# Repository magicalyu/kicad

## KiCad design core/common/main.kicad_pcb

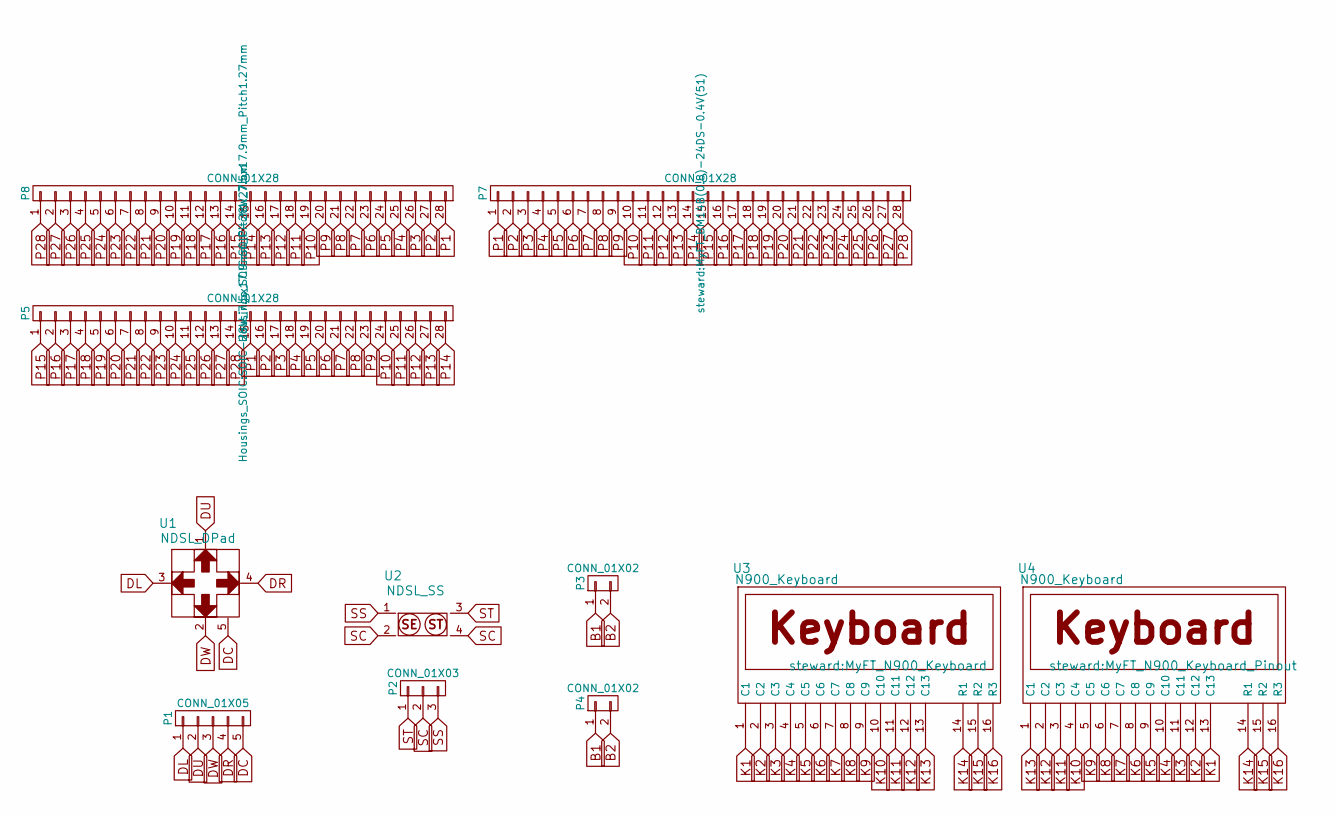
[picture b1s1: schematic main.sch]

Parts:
P1: CONN_01X05; MyFT_SIM5
P2: CONN_01X03; MyFT_SIM3
P3: CONN_01X02; SW_SPST_EVPBF
P4: CONN_01X02; MyFT_SIM2
P5, P8: CONN_01X28; SOIC-28W_7.5x17.9mm_Pitch1.27mm
P7: CONN_01X28; MyFT_BM14B(0.8)-24DS-0.4V(51)
U1: NDSL_DPad; MyFT_NDSL_DPad
U2: NDSL_SS; MyFT_NDSL_SS
U3: N900_Keyboard; MyFT_N900_Keyboard
U4: N900_Keyboard; MyFT_N900_Keyboard_Pinout

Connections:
B1: P3.1, P4.1
B2: P3.2, P4.2
DC: P1.5, U1.5
DL: P1.1, U1.3
DR: P1.4, U1.4
DU: P1.2, U1.1
DW: P1.3, U1.2
K1: U3.1 (C1), U4.13 (C13)
K2: U3.2 (C2), U4.12 (C12)
K3: U3.3 (C3), U4.11 (C11)
K4: U3.4 (C4), U4.10 (C10)
K5: U3.5 (C5), U4.9 (C9)
K6: U3.6 (C6), U4.8 (C8)
K7: U3.7 (C7), U4.7 (C7)
K8: U3.8 (C8), U4.6 (C6)
K9: U3.9 (C9), U4.5 (C5)
K10: U3.10 (C10), U4.4 (C4)
K11: U3.11 (C11), U4.3 (C3)
K12: U3.12 (C12), U4.2 (C2)
K13: U3.13 (C13), U4.1 (C1)
K14: U3.14 (R1), U4.14 (R1)
K15: U3.15 (R2), U4.15 (R2)
K16: U3.16 (R3), U4.16 (R3)
P1: P5.15, P7.1, P8.28
P2: P5.16, P7.2, P8.27
P3: P5.17, P7.3, P8.26
P4: P5.18, P7.4, P8.25
P5: P5.19, P7.5, P8.24
P6: P5.20, P7.6, P8.23
P7: P5.21, P7.7, P8.22
P8: P5.22, P7.8, P8.21
P9: P5.23, P7.9, P8.20
P10: P5.24, P7.10, P8.19
P11: P5.25, P7.11, P8.18
P12: P5.26, P7.12, P8.17
P13: P5.27, P7.13, P8.16
P14: P5.28, P7.14, P8.15
P15: P5.1, P7.15, P8.14
P16: P5.2, P7.16, P8.13
P17: P5.3, P7.17, P8.12
P18: P5.4, P7.18, P8.11
P19: P5.5, P7.19, P8.10
P20: P5.6, P7.20, P8.9
P21: P5.7, P7.21, P8.8
P22: P5.8, P7.22, P8.7
P23: P5.9, P7.23, P8.6
P24: P5.10, P7.24, P8.5
P25: P5.11, P7.25, P8.4
P26: P5.12, P7.26, P8.3
P27: P5.13, P7.27, P8.2
P28: P5.14, P7.28, P8.1
SC: P2.2, U2.2, U2.4
SS: P2.3, U2.1
ST: P2.1, U2.3

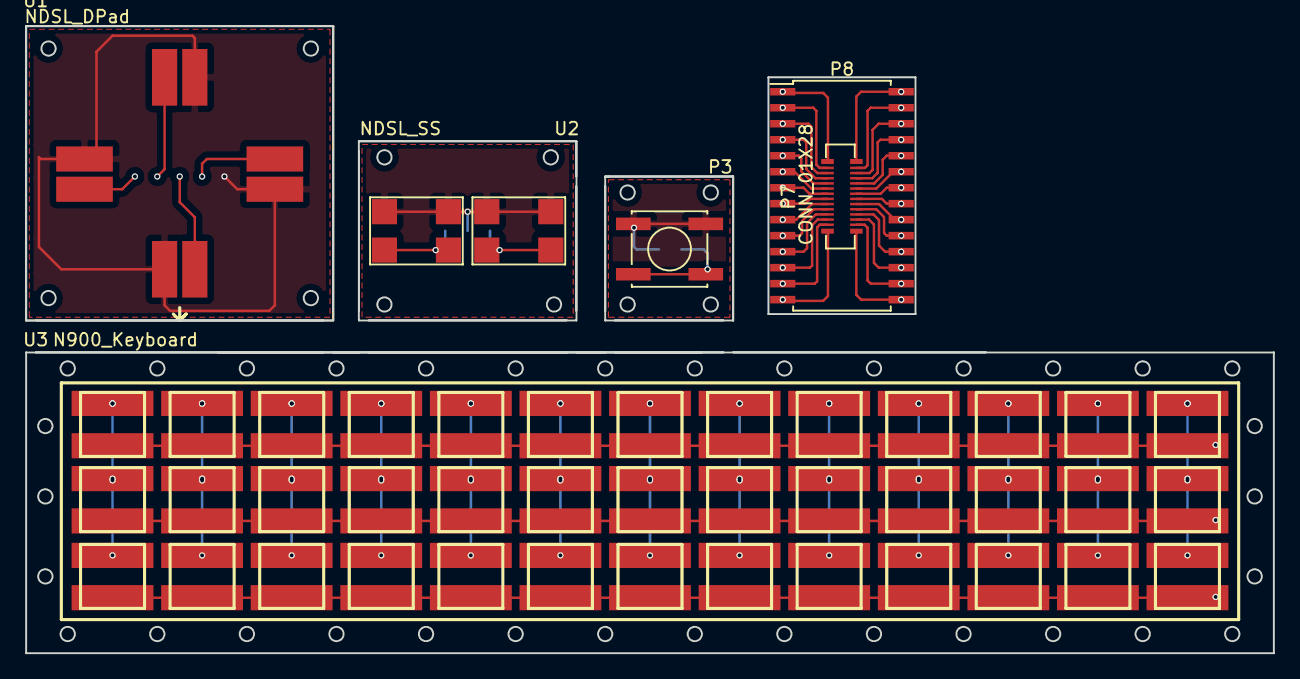
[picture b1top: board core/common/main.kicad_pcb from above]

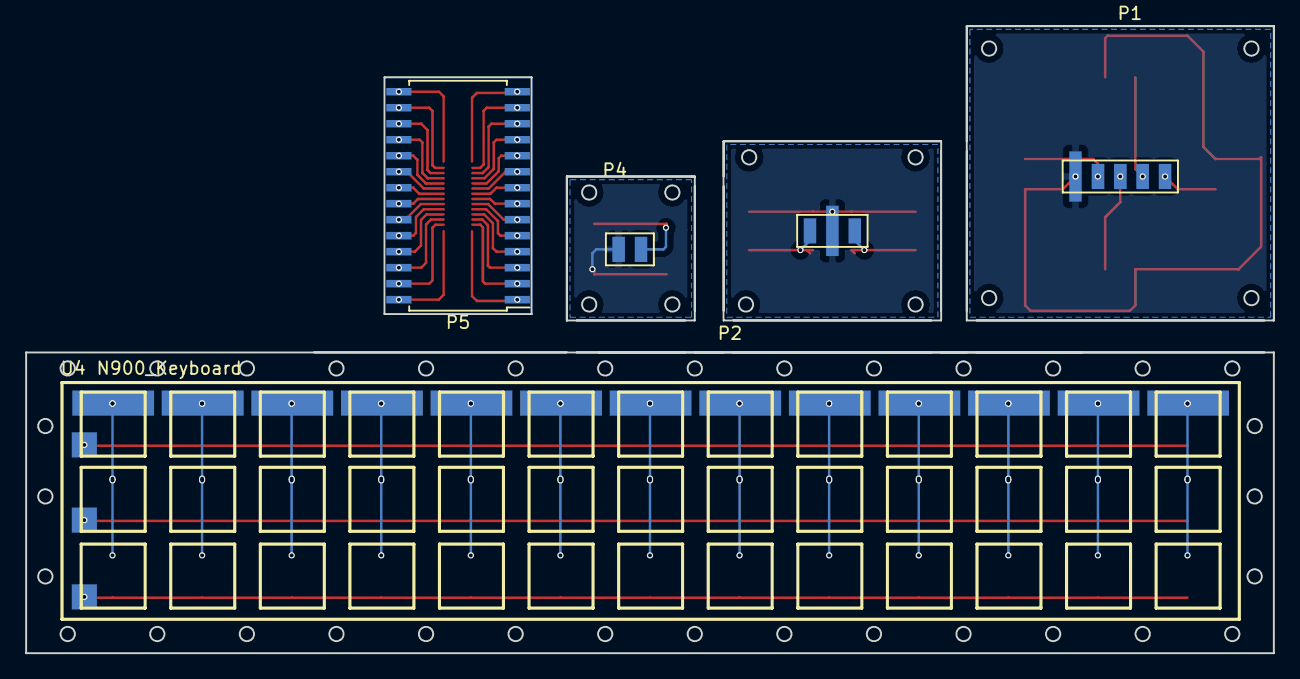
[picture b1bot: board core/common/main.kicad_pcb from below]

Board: 2 copper layers, 99.1 x 49.8 mm, 11 parts (5 on the bottom side), 54 nets.

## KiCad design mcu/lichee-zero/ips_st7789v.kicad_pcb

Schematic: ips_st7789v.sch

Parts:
P1: CONN_01X05
U1: IPS_2.4_240X320_ST7789V
U2: LICHEE_ZERO_LCD

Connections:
CS: P1.2, U1.8
DB0: U1.18, U2.23
DB1: U1.19, U2.24
DB2: U1.20, U2.25
DB3: U1.21, U2.26
DB4: U1.22, U2.27
DB5: U1.23, U2.28
DB6: U1.24, U2.15
DB7: U1.25, U2.16
DB8: U1.26, U2.17
DB9: U1.27, U2.18
DB10: U1.28, U2.19
DB11: U1.30, U2.20
DB12: U1.31, U2.7
DB13: U1.32, U2.8
DB14: U1.33, U2.9
DB15: U1.34, U2.10
DEN: U1.14, U2.34
GND: U1.1, U1.5, U1.17, U1.29, U1.37, U1.38, U1.39, U1.40, U1.41, U1.42, U1.43, U1.44, U1.45, U2.3
HSYNC: U1.13, U2.32
PCLK: U1.15, U2.30
RESET: P1.1, U1.7
SCL: P1.3, U1.9
SDI: P1.4, U1.16
SDO: P1.5, U1.35
VCC: U1.2, U1.3, U1.4, U1.6, U1.10, U1.11, U1.36, U2.4
VSYNC: U1.12, U2.33

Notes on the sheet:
PCB for LiChee_Zero LCD to 2.8" IPS ST7789V

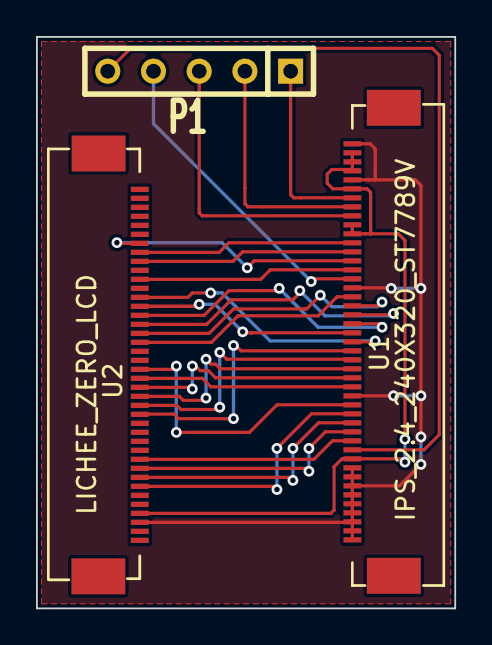
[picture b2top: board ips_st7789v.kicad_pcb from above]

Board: 2 copper layers, 23.2 x 31.8 mm, 3 parts (0 on the bottom side), 27 nets.

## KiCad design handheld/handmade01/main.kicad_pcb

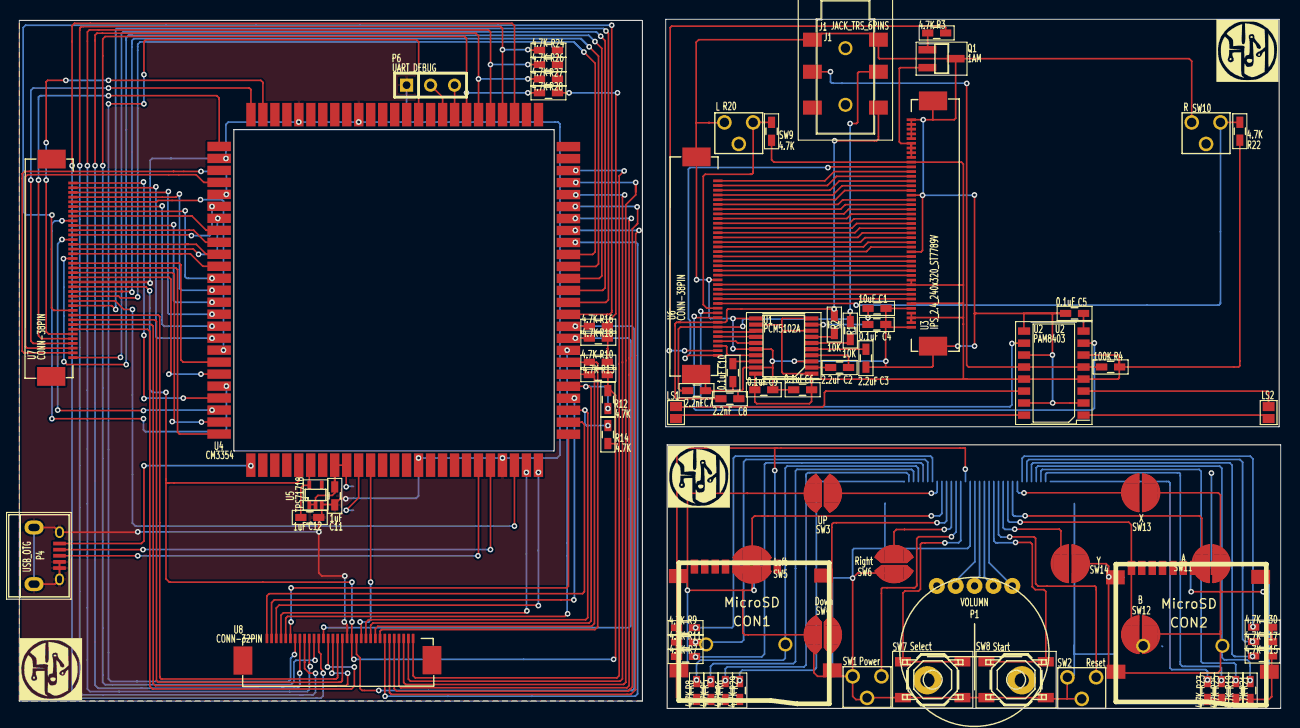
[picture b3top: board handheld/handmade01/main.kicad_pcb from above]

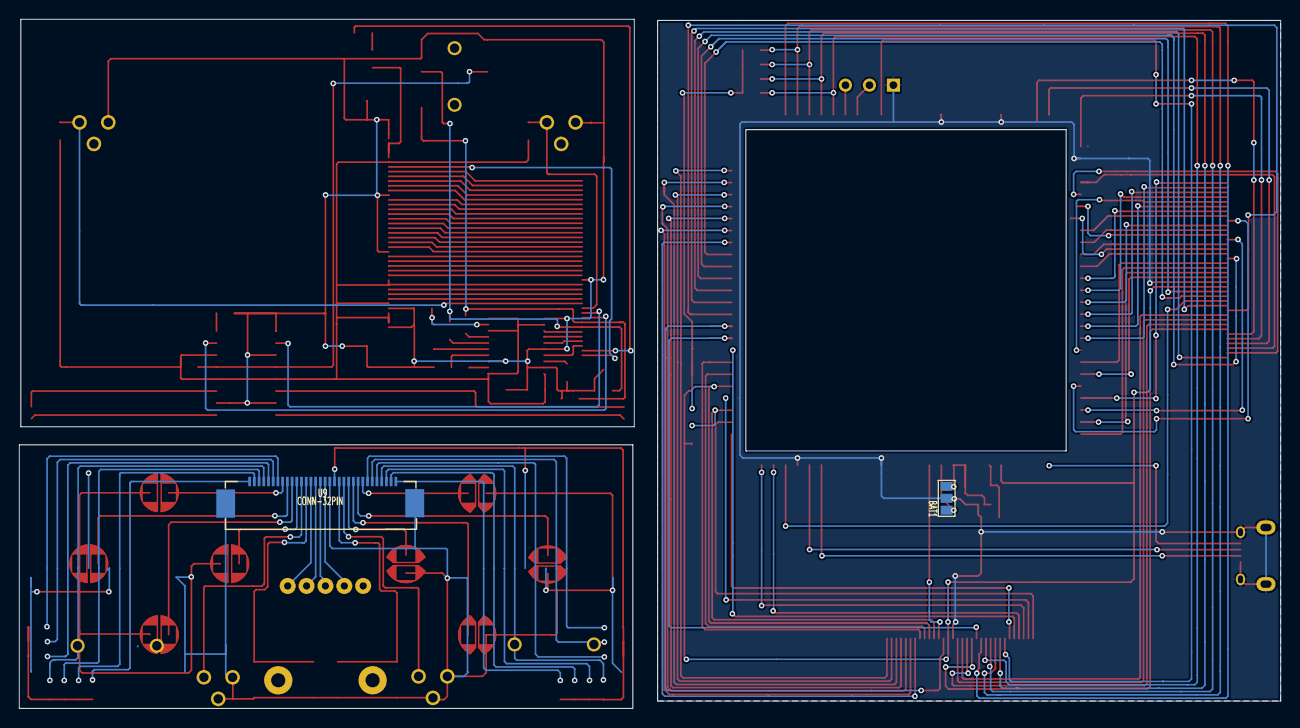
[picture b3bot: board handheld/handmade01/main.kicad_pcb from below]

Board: 2 copper layers, 133.7 x 73.0 mm, 75 parts (2 on the bottom side), 157 nets.

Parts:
BAT1: BAT; GS3
C1: 10uF; MyFT_C_0603
C2, C3: 2.2uF; MyFT_C_0603
C4, C5, C6, C9, C10: 0.1uF; MyFT_C_0603
C7, C8: 2.2nF; MyFT_C_0603
C11, C12: 1uF; MyFT_C_0603
CON1, CON2: MicroSD; MyFT_MicroSD
J1: JACK_TRS_6PINS; MyFT_PJ311_3.5mm
LS1: SPEAKER_R; GS2
LS2: SPEAKER_L; GS2
P1: VOLUMN; MyFT_Volumn
P4: USB_OTG; MyFT_USB_Micro-B
P6: UART_DEBUG; SIL-3
Q1: 1AM; MyFT_SOT-23_Handsoldering
R1, R2: 10K; MyFT_R_0603
R3, R5, R6, R7, R8, R9, R10, R11, R12, R13, R14, R15, R16, R17, R18, R19, R20, R21, R22, R23, R24, R25, R26, R27, R28, R29, R30: 4.7K; MyFT_R_0603
R4: 100K; MyFT_R_0603
SW1: Power; MyFT_4.5x4.5_TS-026-3
SW2: Reset; MyFT_4.5x4.5_TS-026-3
SW3: UP; MyFT_GamePad_Circle_Cut
SW4: Down; MyFT_GamePad_Circle_Cut
SW5: Left; MyFT_GamePad_Circle_Cut
SW6: Right; MyFT_GamePad_Circle_Cut
SW7: Select; MyFT_SW_SPST_TL3342
SW8: Start; MyFT_SW_SPST_TL3342
SW9: L; MyFT_4.5x4.5_TS-026-3
SW10: R; MyFT_4.5x4.5_TS-026-3
SW11: A; MyFT_GamePad_Circle
SW12: B; MyFT_GamePad_Circle
SW13: X; MyFT_GamePad_Circle
SW14: Y; MyFT_GamePad_Circle
U1: PCM5102A; MyFT_TSSOP-20_4.4x6.5mm_Pitch0.65mm
U2: PAM8403; MyFT_SOP-16_4.4x10.4mm_Pitch1.27mm
U3: IPS_2.4_240x320_ST7789V; MyFT_FPC_45_0.5mm_Rev
U4: CM3354; MyFT_CM3354_SMD
U5: TPS71718; MyFT_SC-70-5
U6, U7: CONN-38PIN; MyFT_FPC_38_0.5mm
U8, U9: CONN-32PIN; MyFT_FPC_32_0.5mm

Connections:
+3.3V: R10.1, R12.1, R13.1, R14.1, R16.1, R18.1, R24.1, R26.1, R27.1, R28.1, U4.5, U7.16, U8.14
+5V: P4.1, U4.1
A: SW11.1, U9.24
AUDIO_BCK: U1.13, U6.6
AUDIO_DIN: U1.14, U6.5
AUDIO_LRCK: U1.15, U6.4
AUDIO_MUTE: U1.17, U6.3
B: SW12.1, U9.23
B0_A: R24.2, U4.54, U8.24
B0_AUDIO_BCK: U4.74, U7.6
B0_AUDIO_DIN: U4.76, U7.5
B0_AUDIO_LRCK: U4.75, U7.4
B0_AUDIO_MUTE: U4.79, U7.3
B0_B: R26.2, U4.55, U8.23
B0_DOWN: R12.2, U4.30, U8.10
B0_INL: U7.9, U8.16
B0_INR: U7.10, U8.17
B0_L: U4.36, U7.11
B0_LCD_CS: U4.41, U7.14
B0_LCD_DB0: U4.86, U7.23
B0_LCD_DB1: U4.82, U7.24
B0_LCD_DB2: U4.85, U7.25
B0_LCD_DB3: U4.98, U7.26
B0_LCD_DB4: U4.81, U7.27
B0_LCD_DB5: U4.84, U7.28
B0_LCD_DB6: U4.89, U7.29
B0_LCD_DB7: U4.96, U7.30
B0_LCD_DB8: U4.83, U7.31
B0_LCD_DB9: U4.87, U7.32
B0_LCD_DB10: U4.91, U7.33
B0_LCD_DB11: U4.93, U7.34
B0_LCD_DB12: U4.88, U7.35
B0_LCD_DB13: U4.90, U7.36
B0_LCD_DB14: U4.92, U7.37
B0_LCD_DB15: U4.97, U7.38
B0_LCD_ENABLE: U4.100, U7.20
B0_LCD_HSYNC: U4.99, U7.19
B0_LCD_PCLK: U4.94, U7.21
B0_LCD_RESET: U4.23, U7.13
B0_LCD_SCL: U4.40, U7.15
B0_LCD_SDI: U4.39, U7.22
B0_LCD_SDO: U4.38, U7.1
B0_LCD_VSYNC: U4.95, U7.18
B0_LED_PWM: U4.80, U7.2
B0_LEFT: R13.2, U4.31, U8.9
B0_OUTL: U7.7, U8.19
B0_OUTR: U7.8, U8.18
B0_POWER: U4.11, U8.12
B0_R: U4.37, U7.12
B0_RESET: U4.53, U8.21
B0_RIGHT: R14.2, U4.28, U8.11
B0_SD0_CD: U4.48, U8.1
B0_SD0_CLK: U4.45, U8.5
B0_SD0_CMD: U4.44, U8.4
B0_SD0_DAT0: U4.43, U8.6
B0_SD0_DAT1: U4.42, U8.7
B0_SD0_DAT2: U4.46, U8.2
B0_SD0_DAT3: U4.47, U8.3
B0_SD1_CD: U4.61, U8.26
B0_SD1_CLK: U4.25, U8.30
B0_SD1_CMD: U4.24, U8.29
B0_SD1_DAT0: U4.29, U8.31
B0_SD1_DAT1: U4.27, U8.32
B0_SD1_DAT2: U4.26, U8.27
B0_SD1_DAT3: U4.33, U8.28
B0_SELECT: R16.2, U4.35, U8.13
B0_START: R18.2, U4.34, U8.20
B0_UP: R10.2, U4.32, U8.8
B0_X: R27.2, U4.56, U8.25
B0_Y: R28.2, U4.57, U8.22
B1_3.3V: CON1.4, CON2.4, R5.1, R6.1, R7.1, R8.1, R9.1, R11.1, R15.1, R17.1, R19.1, R21.1, R23.1, R25.1, R29.2, R30.1, U9.14
B1_GND: CON1.6, CON1.10, CON2.6, CON2.10, SW1.2, SW2.2, SW3.2, SW4.2, SW5.2, SW6.2, SW7.2, SW8.2, SW11.2, SW12.2, SW13.2, SW14.2, U9.15
B2_3.3V: C6.2, C9.2, R4.1, R20.1, R22.1, U1.1, U1.8, U1.10, U1.12, U1.20, U2.4, U2.6, U2.13, U3.2, U3.3, U3.4, U3.6, U3.10, U3.11, U3.36, U6.16
B2_GND: C1.2, C3.2, C4.2, C5.2, C6.1, C7.1, C8.1, C9.1, C10.2, J1.1, J1.4, Q1.3, SW9.2, SW10.2, U1.3, U1.11, U1.16, U1.19, U2.2, U2.9, U2.11, U2.15, U3.1, U3.5, U3.17, U3.29, U3.41, U3.42, U3.43, U3.44, U3.45, U6.17
B2_INL: U2.7, U6.9
B2_INR: U2.10, U6.10
B2_OUTL: C7.2, J1.5, R1.2, U6.7
B2_OUTR: C8.2, J1.6, R2.2, U6.8
BAT_+: BAT1.1, C11.2, U4.8, U4.9, U5.1, U5.2
BAT_T: BAT1.3, U4.10
DOWN: SW4.1, U9.10
GND: BAT1.2, C11.1, C12.1, P4.4, P4.5, P4.6, P6.1, U4.15, U4.22, U4.66, U4.71, U4.77, U5.3, U7.17, U8.15
INL: P1.4, U9.16
INR: P1.3, U9.17
L: R20.2, SW9.1, U6.11
LCD_CS: U3.8, U6.14
LCD_DB0: U3.18, U6.23
LCD_DB1: U3.19, U6.24
LCD_DB2: U3.20, U6.25
LCD_DB3: U3.21, U6.26
LCD_DB4: U3.22, U6.27
LCD_DB5: U3.23, U6.28
LCD_DB6: U3.24, U6.29
LCD_DB7: U3.25, U6.30
LCD_DB8: U3.26, U6.31
LCD_DB9: U3.27, U6.32
LCD_DB10: U3.28, U6.33
LCD_DB11: U3.30, U6.34
LCD_DB12: U3.31, U6.35
LCD_DB13: U3.32, U6.36
LCD_DB14: U3.33, U6.37
LCD_DB15: U3.34, U6.38
LCD_ENABLE: U3.14, U6.20
LCD_HSYNC: U3.13, U6.19
LCD_PCLK: U3.15, U6.21
LCD_RESET: U3.7, U6.13
LCD_SCL: U3.9, U6.15
LCD_SDI: U3.16, U6.22
LCD_SDO: U3.35, U6.1
LCD_VSYNC: U3.12, U6.18
LED_K: Q1.2, U3.37, U3.38, U3.39, U3.40
LED_PWM: R3.2, U6.2
LEFT: SW5.1, U9.9
MUTE: J1.2, R4.2, U2.5, U2.12
unnamed: C2.2, U1.2
unnamed: R1.1, U1.6
unnamed: R2.1, U1.7
unnamed: C2.1, U1.4
unnamed: C3.1, U1.5
unnamed: C10.1, U1.18
unnamed: C1.1, C4.1, U1.9
unnamed: Q1.1, R3.1
unnamed: C5.1, U2.8
OUTL: P1.1, U9.19
OUTR: P1.2, U9.18
OUT_L+: LS2.1, U2.1
OUT_L-: LS2.2, U2.3
OUT_R+: LS1.1, U2.16
OUT_R-: LS1.2, U2.14
POWER: SW1.1, U9.12
R: R22.2, SW10.1, U6.12
RESET: SW2.1, U9.21
RIGHT: SW6.1, U9.11
RTC_+: C12.2, U4.6, U5.5
SD0_CD: CON1.9, R29.1, U9.1
SD0_CLK: CON1.5, R7.2, U9.5
SD0_CMD: CON1.3, R8.2, U9.4
SD0_DAT0: CON1.7, R11.2, U9.6
SD0_DAT1: CON1.8, R9.2, U9.7
SD0_DAT2: CON1.1, R6.2, U9.2
SD0_DAT3: CON1.2, R5.2, U9.3
SD1_CD: CON2.9, R30.2, U9.26
SD1_CLK: CON2.5, R19.2, U9.30
SD1_CMD: CON2.3, R21.2, U9.29
SD1_DAT0: CON2.7, R25.2, U9.31
SD1_DAT1: CON2.8, R23.2, U9.32
SD1_DAT2: CON2.1, R17.2, U9.27
SD1_DAT3: CON2.2, R15.2, U9.28
SELECT: SW7.1, U9.13
START: SW8.1, U9.20
UART_RX: P6.3, U4.58
UART_TX: P6.2, U4.59
UP: SW3.1, U9.8
USB_DM: P4.2, U4.21
USB_DP: P4.3, U4.20
X: SW13.1, U9.25
Y: SW14.1, U9.22

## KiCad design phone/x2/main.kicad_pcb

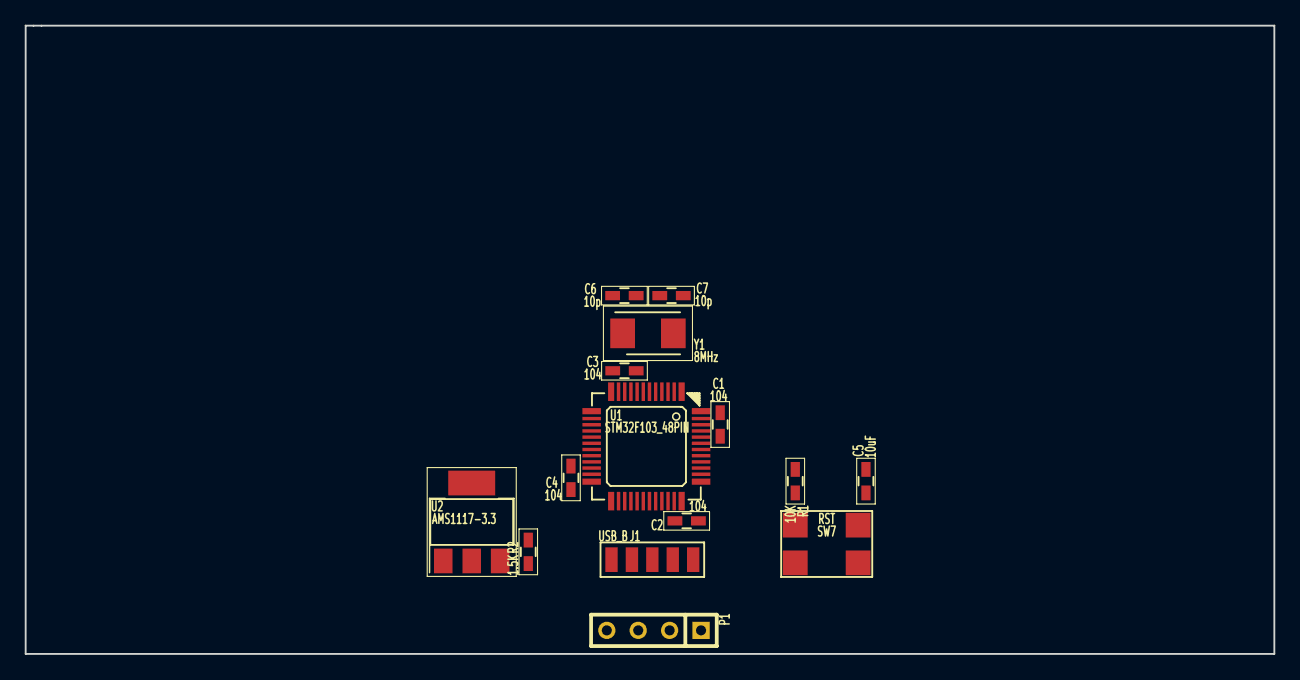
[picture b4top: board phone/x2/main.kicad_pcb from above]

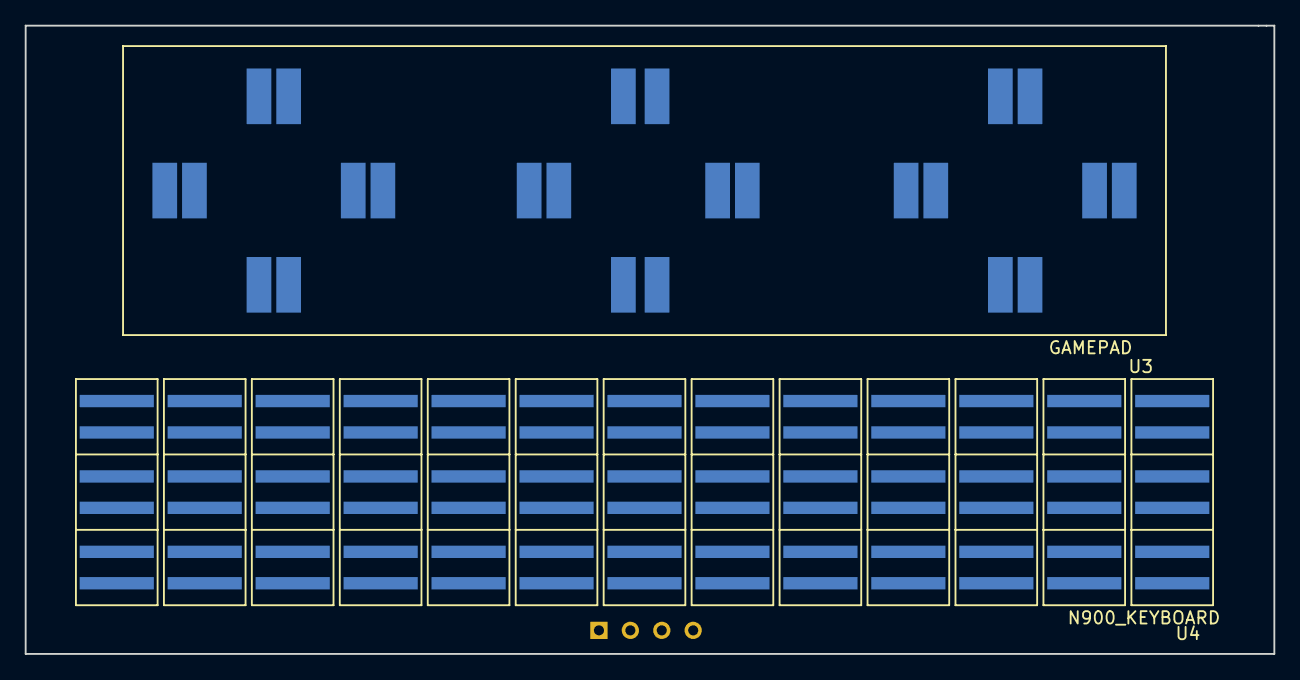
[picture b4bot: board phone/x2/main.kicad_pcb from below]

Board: 2 copper layers, 101.0 x 50.8 mm, 17 parts (2 on the bottom side), 22 nets, no tracks yet.

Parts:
C1, C2, C3, C4: 104; MyFT_C_0603
C5: 10uF; MyFT_C_0603
C6, C7: 10p; MyFT_C_0603
J1: USB_B; MyFT_USB_Mini_B_PIN_ONLY
P1: CONN_4; SIL-4
R1: 10K; MyFT_R_0603
R2: 1.5K; MyFT_R_0603
SW7: RST; MyFT_4.5x4.5_SMD
U1: STM32F103_48PIN; MyFT_LQFP-48-1EP_7x7mm_Pitch0.5mm
U2: AMS1117-3.3; MyFT_SOT-223
U3: GAMEPAD; MyFT_GamePad_For_X2
U4: N900_KEYBOARD; MyFT_N900_Keyboard
Y1: 8MHz; MyFT_Crystal_SMD_5032_2Pads

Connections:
+3.3V: C1.1, C2.1, C3.1, C4.1, P1.4, R1.1, U1.9, U1.24, U1.36, U1.48, U2.2
+5V: J1.1, R2.1, U2.3
A: U1.11, U3.5
B: U1.12, U3.6
DOWN: U1.3, U3.2
GND: C1.2, C2.2, C3.2, C4.2, C5.2, C6.2, C7.2, J1.4, J1.5, P1.3, SW7.2, U1.8, U1.23, U1.35, U1.44, U1.47, U2.1, U3.13
L: U1.17, U3.11
LEFT: U1.4, U3.3
R: U1.18, U3.12
RIGHT: U1.10, U3.4
RST: C5.1, R1.2, SW7.1, U1.7
SELECT: U1.15, U3.9
START: U1.16, U3.10
SWCLK: P1.1, U1.37
SWDIO: P1.2, U1.34
UP: U1.2, U3.1
USB_DM: J1.2, U1.32
USB_DP: J1.3, R2.2, U1.33
X: U1.13, U3.7
X1: C7.1, U1.5, Y1.2
X2: C6.1, U1.6, Y1.1
Y: U1.14, U3.8

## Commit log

2018-07-06 init
2018-08-14 upgraded to new kicad
2018-08-14 updated core/common
2018-08-21 updated library
2018-08-21 updated core library
2018-10-12 updated for ndsl_dpad, ndsl_ss, ndsl_lr, n900_keyboard
2018-10-12 combine pcb
2018-10-18 updated n900 and blackberry q30 sch & pcb
2018-10-18 updated n900 pcb
